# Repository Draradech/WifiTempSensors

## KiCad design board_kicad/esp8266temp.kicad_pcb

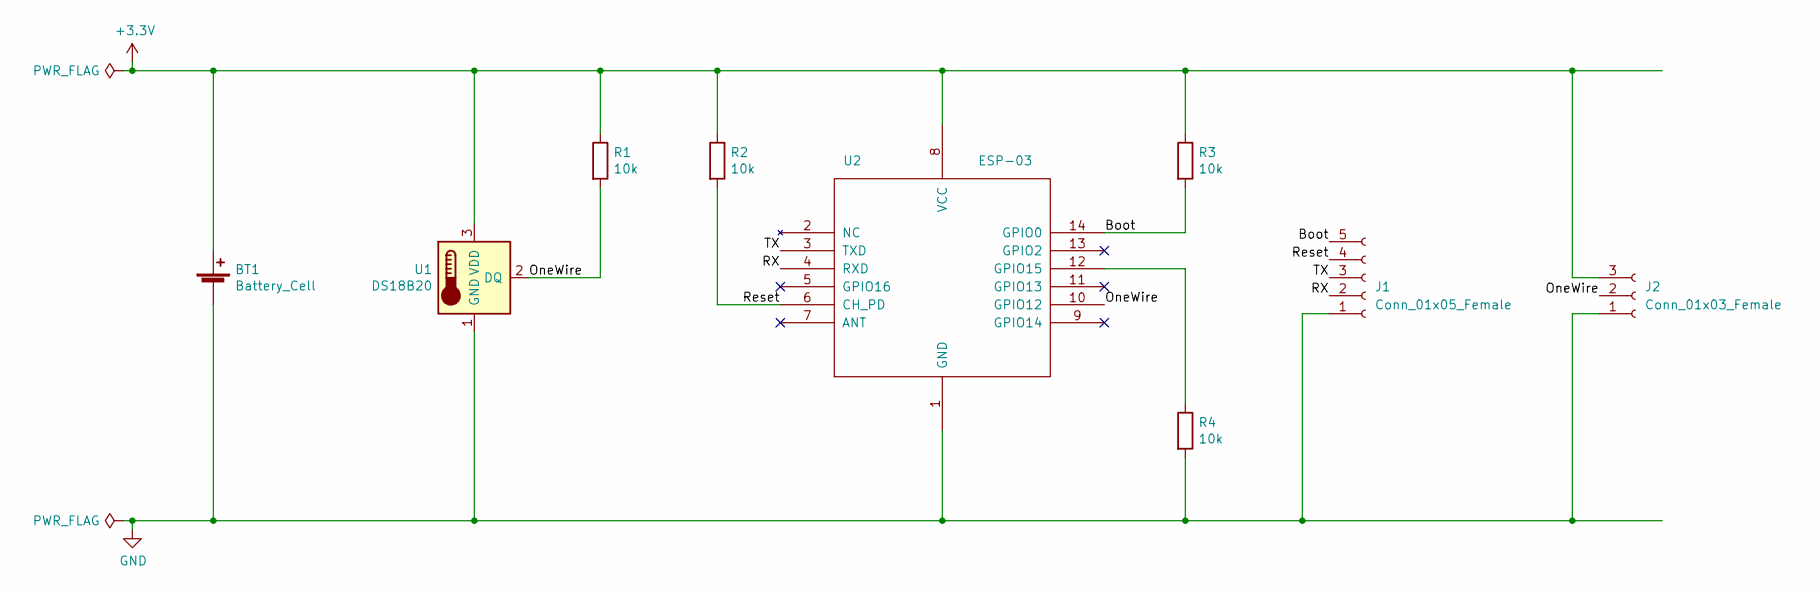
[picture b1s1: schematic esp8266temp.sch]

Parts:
BT1: Battery_Cell; BLM_26650
J1: Conn_01x05_Female; PinHeader_1x05_P2.54mm_Vertical
J2: Conn_01x03_Female; PinHeader_1x03_P2.54mm_Vertical
R1, R2, R3, R4: 10k; R_Axial_DIN0207_L6.3mm_D2.5mm_P10.16mm_Horizontal
U1: DS18B20; TO-92_Inline
U2: ESP-03

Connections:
+3V3: BT1.1 (+), J2.3, R1.1, R2.1, R3.1, U1.3 (VDD), U2.8 (VCC)
/Boot: J1.5, R3.2, U2.14 (GPIO0)
/OneWire: J2.2, R1.2, U1.2 (DQ), U2.10 (GPIO12)
/RX: J1.2, U2.4 (RXD)
/Reset: J1.4, R2.2, U2.6 (CH_PD)
/TX: J1.3, U2.3 (TXD)
GND: BT1.2 (-), J1.1, J2.1, R4.2, U1.1 (GND), U2.1 (GND)
unnamed: R4.1, U2.12 (GPIO15)

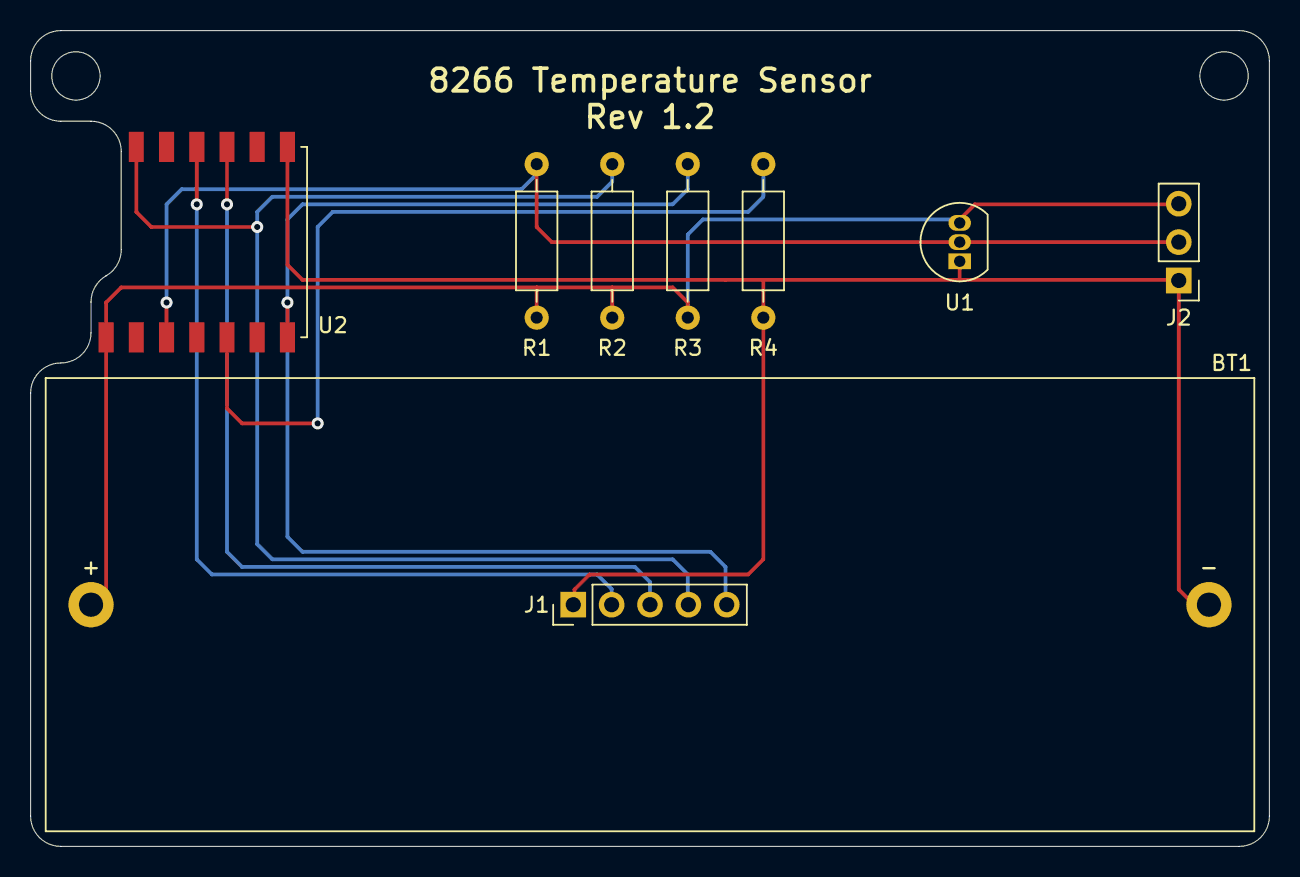
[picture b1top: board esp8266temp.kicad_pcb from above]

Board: 2 copper layers, 82.0 x 54.0 mm, 11 parts (0 on the bottom side), 8 nets.

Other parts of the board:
3mm, 3mm#2: MountingHole_2.2mm_M2

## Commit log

2021-08-08 add firmware file
2021-08-08 fix tabs/spaces
2021-08-08 add host src files
2021-08-08 add server files
2021-08-08 add kicad board files
2021-08-08 add setup firmware
